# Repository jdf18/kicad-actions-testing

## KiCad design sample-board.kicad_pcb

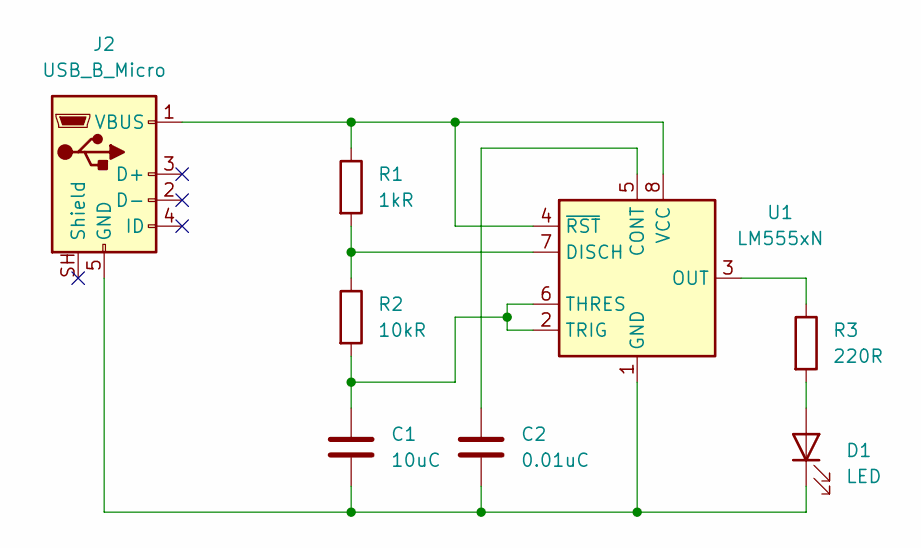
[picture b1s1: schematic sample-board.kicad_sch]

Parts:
C1: 10uC; C_Disc_D5.0mm_W2.5mm_P2.50mm
C2: 0.01uC; C_Disc_D5.0mm_W2.5mm_P2.50mm
D1: LED; LED_D3.0mm
J2: USB_B_Micro; USB_Micro-AB_Molex_47590-0001
R1: 1kR; R_Axial_DIN0207_L6.3mm_D2.5mm_P2.54mm_Vertical
R2: 10kR; R_Axial_DIN0207_L6.3mm_D2.5mm_P2.54mm_Vertical
R3: 220R; R_Axial_DIN0207_L6.3mm_D2.5mm_P2.54mm_Vertical
U1: LM555xN; DIP-8_W7.62mm

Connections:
unnamed: D1.2 (A), R3.2
unnamed 1: C1.2, C2.2, D1.1 (K), J2.5 (GND), U1.1 (GND); also elsewhere on the board
unnamed 2: J2.1 (VBUS), R1.1, U1.4 (~RST), U1.8 (VCC); also elsewhere on the board
unnamed: C2.1, U1.5 (CONT)
unnamed: R1.2, R2.1, U1.7 (DISCH)
unnamed: R3.1, U1.3 (OUT)
unnamed: C1.1, R2.2, U1.2 (TRIG), U1.6 (THRES)

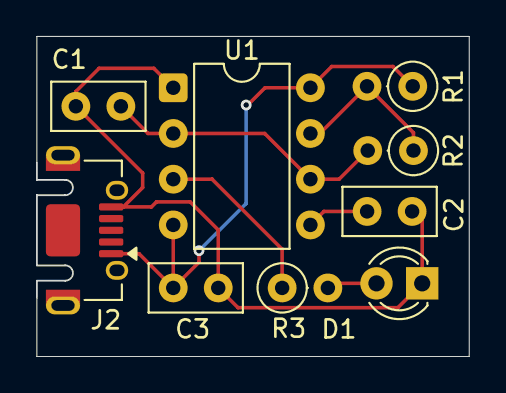
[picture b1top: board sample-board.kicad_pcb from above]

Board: 2 copper layers, 24.0 x 17.7 mm, 9 parts (0 on the bottom side), 7 nets.

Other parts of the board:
C3: 10uC; C_Disc_D5.0mm_W2.5mm_P2.50mm

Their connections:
unnamed 1: C3.2; also elsewhere on the board
unnamed 2: C3.1; also elsewhere on the board

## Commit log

2026-05-17 Test board: LED Blinker
2026-05-17 Add readme
2026-05-17 fixing board names
2026-05-17 Modifying silkscreen positions
2026-05-17 Updating badge urls
2026-05-17 Print errors to console
2026-05-17 Moving silkscreen again
2026-05-17 Adding missing trace
2026-05-17 Release workflow
2026-05-17 Update release.yml permissions
2026-05-17 More release assets
2026-05-17 Fixing errors/warnings
2026-05-17 Updating images to png so supported by markdown
2026-05-17 Fixing output options
2026-05-17 schematic svg to png conversion
2026-05-17 Fixing again
2026-05-17 Adding page numbers
2026-05-18 Hopefully this works now
2026-05-18 Adding links on release page
